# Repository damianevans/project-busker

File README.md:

# Project Busker

I promised I would build my daughter a busking amp for her Birthday. That was 18 months ago 😫
This project is based on the excellent hackaday article from David Silverman (details below).
The final plan is for a self-contained busking amp with the following features:
- 2 XLR microphone inputs, each with it's own pre-amp and reverb module.
- An electric guitar amp with effects, built using a raspberry pi 4 with an AudioInjector hat
- A hardware mixer
- a power amp

# David Silverman's guitarpedal links
Guitar Pedal for Raspberry pi using Python and PYO library 

Technical documentation being worked on here:

https://docs.google.com/presentation/d/1GgiD2UTEGcz-SC2rGDjdIljaK2Yn0Rs03TDFOu3duUw/edit?usp=sharing

Video demo here:

https://www.youtube.com/watch?v=wl24fLW1fQE

In depth code walkthrough here:

https://www.youtube.com/watch?v=LpFfZ5o4mEs

Looper video here:

https://youtu.be/jMI3nN0OYLE

Hackaday project here:

https://hackaday.io/project/186218-raspberry-pi-guitar-amplifier

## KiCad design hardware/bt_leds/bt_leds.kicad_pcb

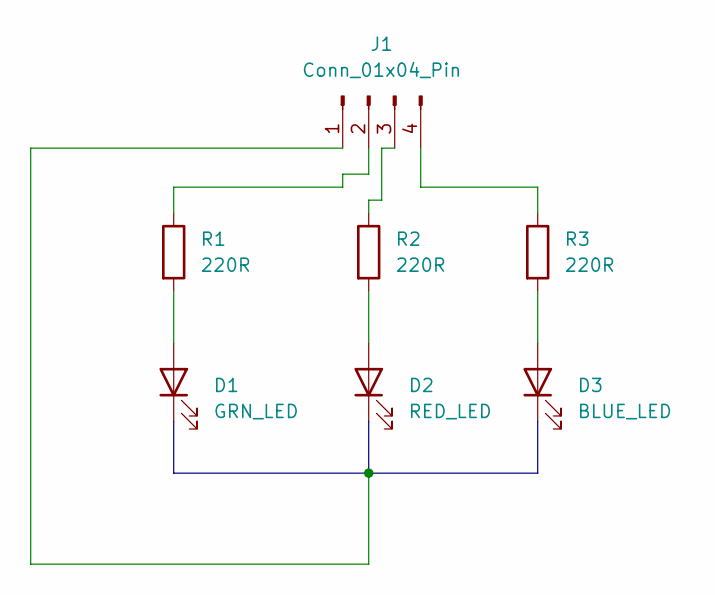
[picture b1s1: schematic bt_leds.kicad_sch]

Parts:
D1: GRN_LED; LED_Rectangular_W5.0mm_H2.0mm
D2: RED_LED; LED_Rectangular_W5.0mm_H2.0mm
D3: BLUE_LED; LED_Rectangular_W5.0mm_H2.0mm
J1: Conn_01x04_Pin; PinHeader_1x04_P2.54mm_Vertical
R1, R2, R3: 220R; R_Axial_DIN0207_L6.3mm_D2.5mm_P10.16mm_Horizontal

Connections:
unnamed: D1.2 (A), R1.2
unnamed: D1.1 (K), D2.1 (K), D3.1 (K), J1.1
unnamed: D2.2 (A), R2.2
unnamed: D3.2 (A), R3.2
unnamed: J1.2, R1.1
unnamed: J1.3, R2.1
unnamed: J1.4, R3.1

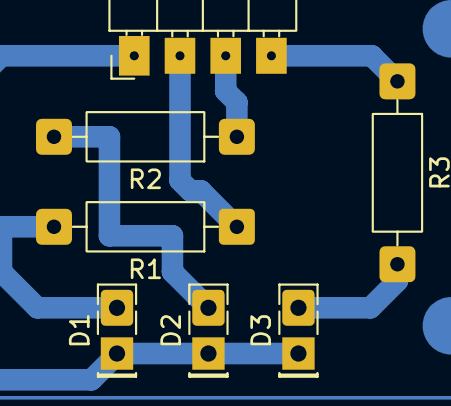
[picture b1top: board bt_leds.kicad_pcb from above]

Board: 2 copper layers, 7 parts (0 on the bottom side), 7 nets.

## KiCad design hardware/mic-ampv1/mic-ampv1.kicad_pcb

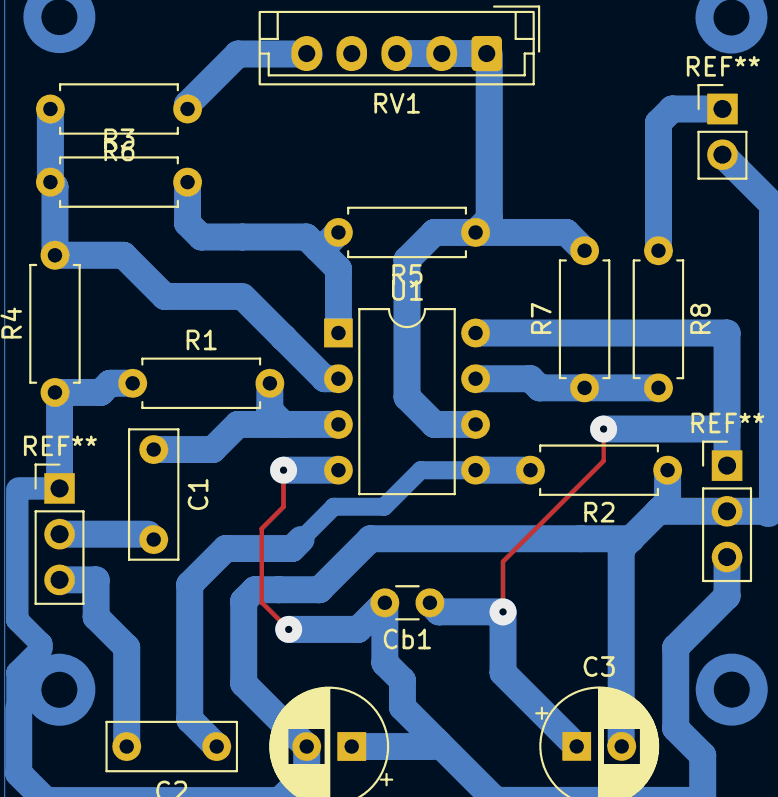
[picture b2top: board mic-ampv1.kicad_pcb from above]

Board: 2 copper layers, 15 parts (0 on the bottom side), 10 nets.

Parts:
C1, C2: 150nF; C_Rect_L7.0mm_W2.5mm_P5.00mm
C3, C4: 10uF; CP_Radial_D6.3mm_P2.50mm
Cb1: 100nF; C_Disc_D3.0mm_W1.6mm_P2.50mm
R1, R2, R3, R4, R5, R7: 10K; R_Axial_DIN0207_L6.3mm_D2.5mm_P7.62mm_Horizontal
R6: 47; R_Axial_DIN0207_L6.3mm_D2.5mm_P7.62mm_Horizontal
R8: 100; R_Axial_DIN0207_L6.3mm_D2.5mm_P7.62mm_Horizontal
RV1: 10K; JST_EH_B5B-EH-A_1x05_P2.50mm_Vertical
U1: NE5532; DIP-8_W7.62mm

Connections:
+12V: C3.1, Cb1.1, U1.8 (V+)
-12V: C4.1, Cb1.2, U1.4 (V-)
Gnd: C3.2, C4.2, R1.1, R2.1, R4.1
unnamed: R3.2, R5.2, U1.1
unnamed: R6.1, RV1.5
unnamed: R7.1, R8.2, U1.7
unnamed: C1.1, R1.2, U1.3 (+)
unnamed: R3.1, R4.2, R6.2, U1.2 (-)
unnamed: C2.1, R2.2, U1.5 (+)
unnamed: R5.1, R7.2, RV1.1, RV1.2, RV1.3, U1.6 (-)

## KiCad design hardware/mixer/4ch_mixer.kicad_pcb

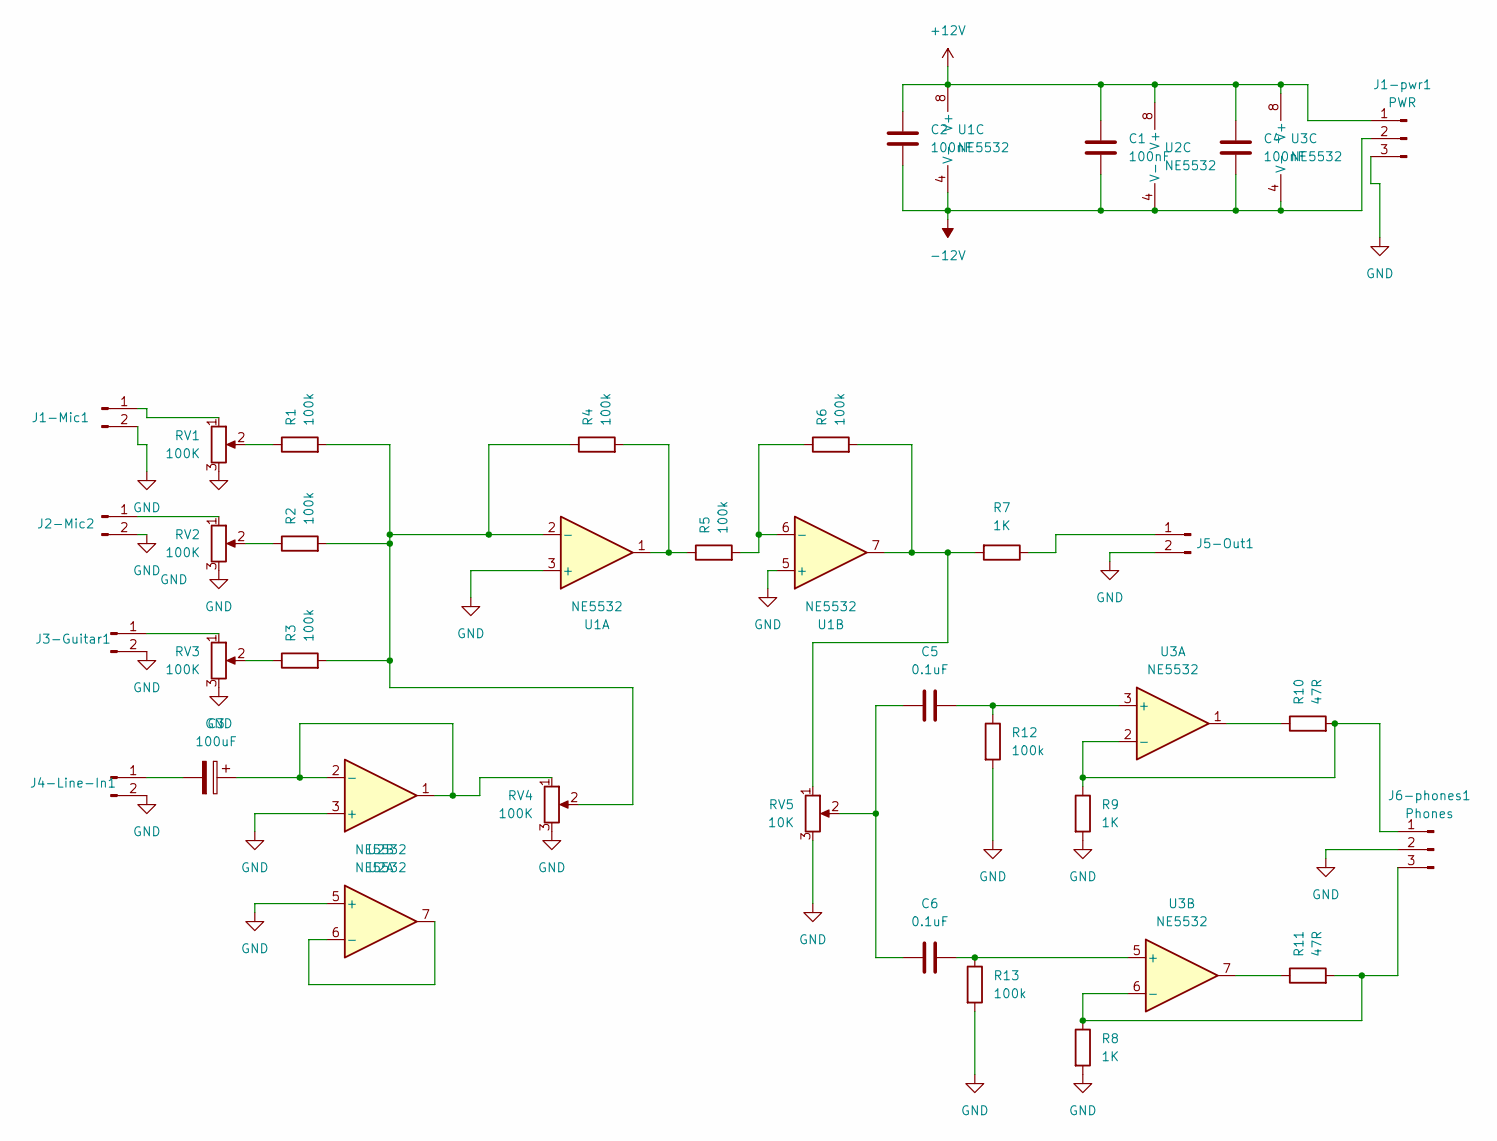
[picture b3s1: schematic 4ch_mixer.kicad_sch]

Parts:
C1, C2, C4: 100nF; C_Disc_D3.0mm_W1.6mm_P2.50mm
C3: 100uF; CP_Radial_D4.0mm_P1.50mm
C5, C6: 0.1uF; C_Rect_L11.0mm_W2.8mm_P10.00mm_MKT
J1-Mic1, J2-Mic2, J3-Guitar1, J4-Line-In1, J5-Out1: Conn_01x02_Pin; PinHeader_1x02_P2.54mm_Vertical
J1-pwr1: PWR; FanPinHeader_1x03_P2.54mm_Vertical
J6-phones1: Phones; FanPinHeader_1x03_P2.54mm_Vertical
R1, R2, R3, R4, R5, R6, R12, R13: 100k; R_Axial_DIN0204_L3.6mm_D1.6mm_P5.08mm_Horizontal
R7, R8, R9: 1K; R_Axial_DIN0204_L3.6mm_D1.6mm_P5.08mm_Horizontal
R10, R11: 47R; R_Axial_DIN0204_L3.6mm_D1.6mm_P5.08mm_Horizontal
RV1, RV2, RV3, RV4: 100K; PinHeader_1x03_P2.54mm_Vertical
RV5: 10K; PinHeader_1x03_P2.54mm_Vertical
U1, U2, U3: NE5532; CERDIP-8_W7.62mm_SideBrazed_LongPads

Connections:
+12V: C1.1, C2.1, C4.1, J1-pwr1.1, U1.8 (V+), U2.8 (V+), U3.8 (V+)
-12V: C1.2, C2.2, C4.2, J1-pwr1.2, U1.4 (V-), U2.4 (V-), U3.4 (V-)
GND: J1-Mic1.2, J1-pwr1.3, J2-Mic2.2, J3-Guitar1.2, J4-Line-In1.2, J5-Out1.2, J6-phones1.2, R8.2, R9.2, R12.2, R13.2, RV1.3, RV2.3, RV3.3, RV4.3, RV5.3, U1.3 (+), U1.5 (+), U2.3 (+), U2.5 (+)
unnamed: C5.1, C6.1, RV5.2
unnamed: J1-Mic1.1, RV1.1
unnamed: J2-Mic2.1, RV2.1
unnamed: J3-Guitar1.1, RV3.1
unnamed: C3.2, J4-Line-In1.1
unnamed: J5-Out1.1, R7.1
unnamed: J6-phones1.1, R9.1, R10.2, U3.2 (-)
unnamed: J6-phones1.3, R8.1, R11.2, U3.6 (-)
unnamed: R1.1, RV1.2
unnamed: R2.1, RV2.2
unnamed: R3.1, RV3.2
unnamed: R4.2, R5.1, U1.1
unnamed: R6.2, R7.2, RV5.1, U1.7
unnamed: R10.1, U3.1
unnamed: R11.1, U3.7
unnamed: R1.2, R2.2, R3.2, R4.1, RV4.2, U1.2 (-)
unnamed: R5.2, R6.1, U1.6 (-)
unnamed: C3.1, RV4.1, U2.1, U2.2 (-)
unnamed: U2.6 (-), U2.7
unnamed: C5.2, R12.1, U3.3 (+)
unnamed: C6.2, R13.1, U3.5 (+)

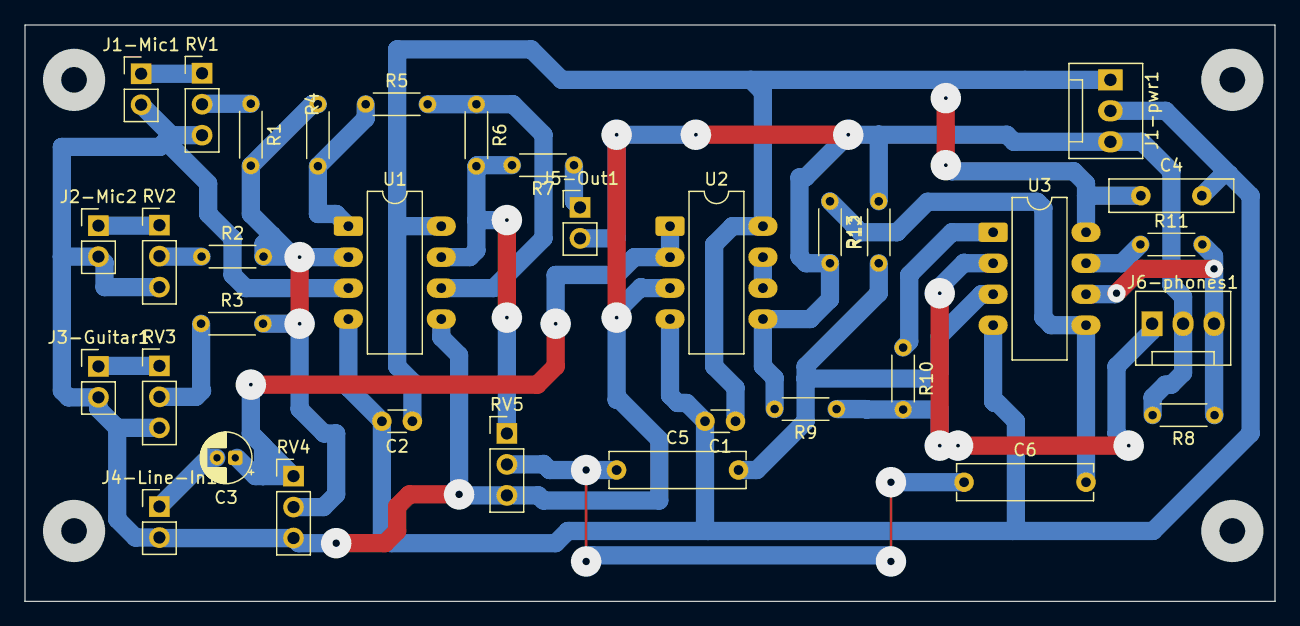
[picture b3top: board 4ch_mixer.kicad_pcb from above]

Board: 2 copper layers, 102.5 x 47.3 mm, 34 parts (0 on the bottom side), 24 nets.

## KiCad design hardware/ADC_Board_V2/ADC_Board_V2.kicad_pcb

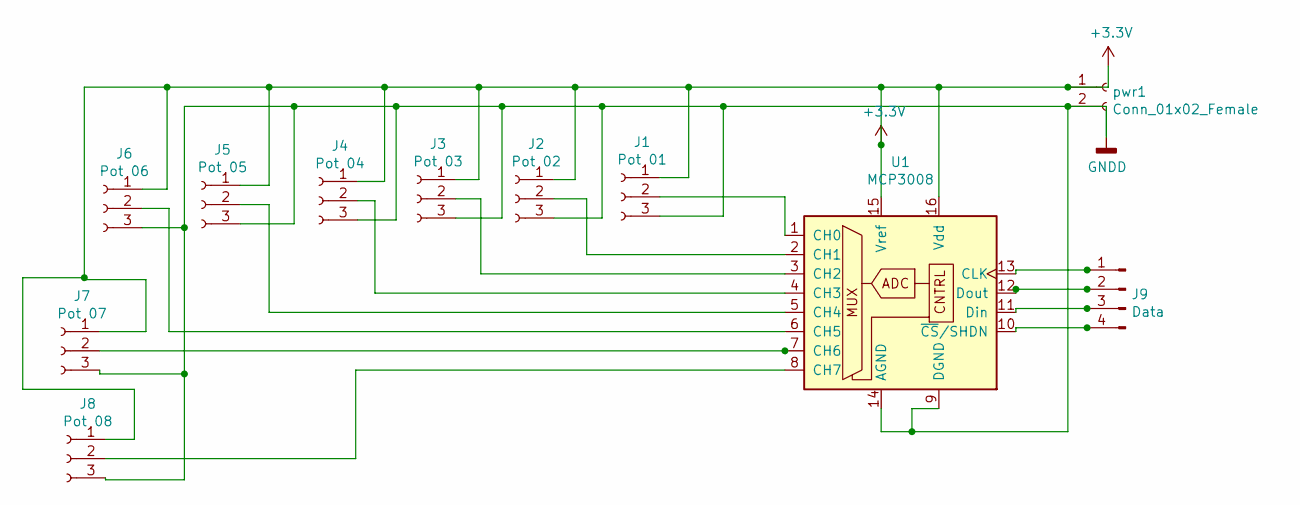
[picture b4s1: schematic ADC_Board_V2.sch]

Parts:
J1: Pot 01; JST_XH_B3B-XH-A_1x03_P2.50mm_Vertical
J2: Pot 02; JST_XH_B3B-XH-A_1x03_P2.50mm_Vertical
J3: Pot 03; JST_XH_B3B-XH-A_1x03_P2.50mm_Vertical
J4: Pot 04; JST_XH_B3B-XH-A_1x03_P2.50mm_Vertical
J5: Pot 05; JST_XH_B3B-XH-A_1x03_P2.50mm_Vertical
J6: Pot 06; JST_XH_B3B-XH-A_1x03_P2.50mm_Vertical
J7: Pot 07; JST_XH_B3B-XH-A_1x03_P2.50mm_Vertical
J8: Pot 08; JST_XH_B3B-XH-A_1x03_P2.50mm_Vertical
J9: Data; PinHeader_1x04_P2.54mm_Horizontal
U1: MCP3008; DIP-16_W7.62mm_Socket_LongPads
pwr1: Conn_01x02_Female; JST_XH_B2B-XH-AM_1x02_P2.50mm_Vertical

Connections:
+3V3: J1.1, J2.1, J3.1, J4.1, J5.1, J6.1, J7.1, J8.1, U1.15 (Vref), U1.16 (Vdd), pwr1.1
GNDD: J1.3, J2.3, J3.3, J4.3, J5.3, J6.3, J7.3, J8.3, U1.9 (DGND), U1.14 (AGND), pwr1.2
unnamed: J1.2, U1.1 (CH0)
unnamed: J2.2, U1.2 (CH1)
unnamed: J3.2, U1.3 (CH2)
unnamed: J4.2, U1.4 (CH3)
unnamed: J5.2, U1.5 (CH4)
unnamed: J6.2, U1.6 (CH5)
unnamed: J7.2, U1.7 (CH6)
unnamed: J8.2, U1.8 (CH7)
unnamed: J9.1, U1.13 (CLK)
unnamed: J9.2, U1.12 (Dout)
unnamed: J9.3, U1.11 (Din)
unnamed: J9.4, U1.10 (~CS~/SHDN)

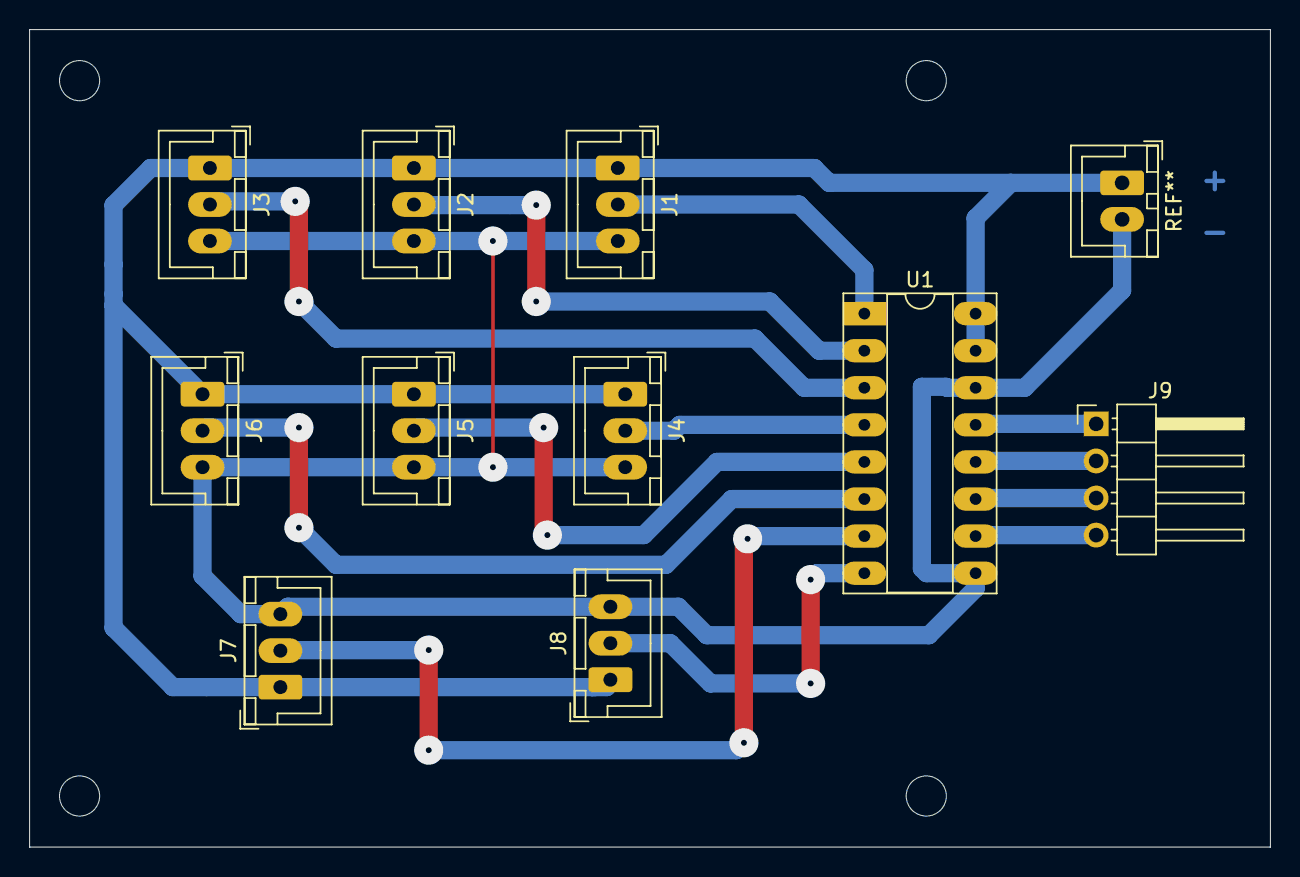
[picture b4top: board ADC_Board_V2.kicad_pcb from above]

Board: 2 copper layers, 85.0 x 56.0 mm, 10 parts (0 on the bottom side), 14 nets.

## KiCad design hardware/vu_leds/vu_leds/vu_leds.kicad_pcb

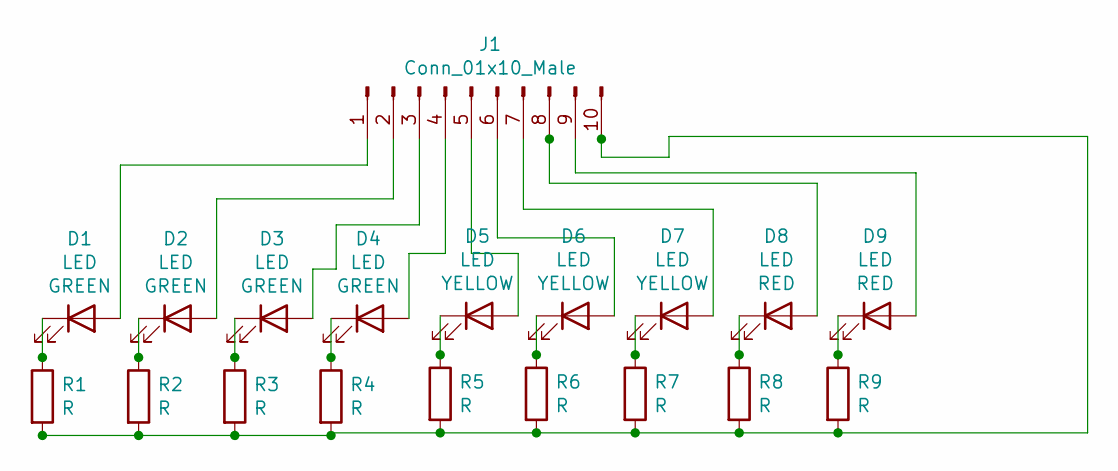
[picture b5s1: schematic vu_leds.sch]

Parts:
D1, D2, D3, D4, D5, D6, D7, D8, D9: LED; LED_Rectangular_W5.0mm_H2.0mm
J1: Conn_01x10_Male; PinHeader_1x10_P2.54mm_Horizontal
R1, R2, R3, R4, R5, R6, R7, R8, R9: R; R_Axial_DIN0207_L6.3mm_D2.5mm_P7.62mm_Horizontal

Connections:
unnamed: D1.1 (K), R1.1
unnamed: D1.2 (A), J1.1
unnamed: D2.1 (K), R2.1
unnamed: D2.2 (A), J1.2
unnamed: D3.1 (K), R3.1
unnamed: D3.2 (A), J1.3
unnamed: D4.1 (K), R4.1
unnamed: D4.2 (A), J1.4
unnamed: D5.1 (K), R5.1
unnamed: D5.2 (A), J1.5
unnamed: D6.1 (K), R6.1
unnamed: D6.2 (A), J1.6
unnamed: D7.1 (K), R7.1
unnamed: D7.2 (A), J1.7
unnamed: D8.1 (K), R8.1
unnamed: D8.2 (A), J1.8
unnamed: D9.1 (K), R9.1
unnamed: D9.2 (A), J1.9
unnamed: J1.10, R1.2, R2.2, R3.2, R4.2, R5.2, R6.2, R7.2, R8.2, R9.2

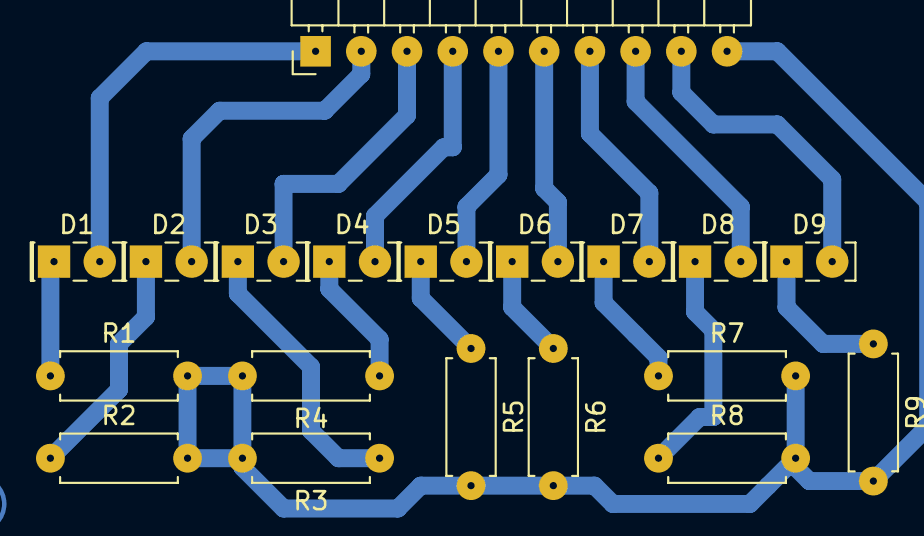
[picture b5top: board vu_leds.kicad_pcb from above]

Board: 2 copper layers, 19 parts (0 on the bottom side), 19 nets.

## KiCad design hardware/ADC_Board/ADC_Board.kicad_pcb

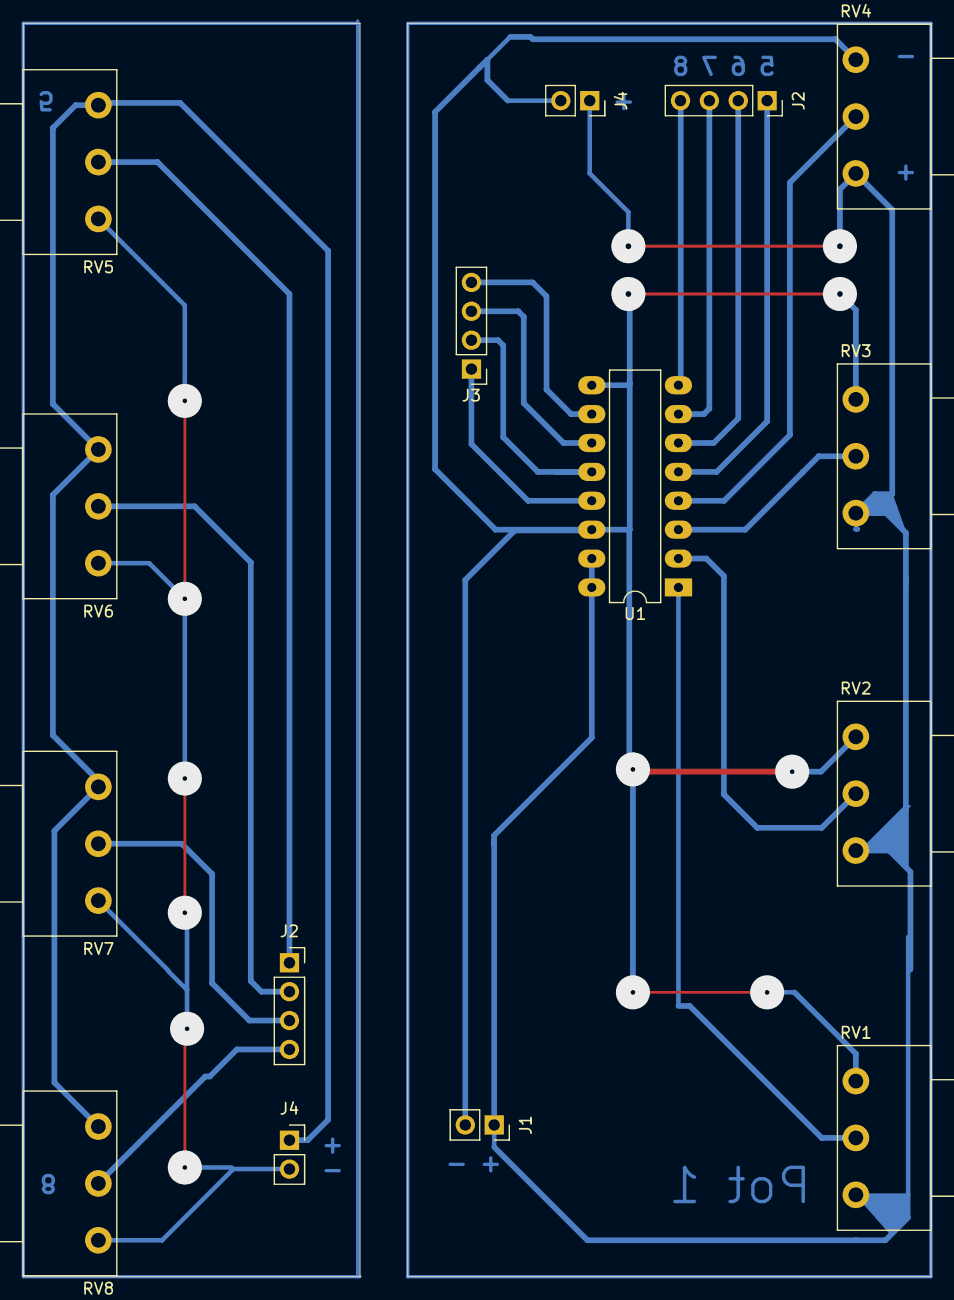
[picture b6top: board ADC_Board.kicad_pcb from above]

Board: 2 copper layers, 79.8 x 110.2 mm, 15 parts (0 on the bottom side), 12 nets.

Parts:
J1, J4, J4#2: Conn_01x02_Female; PinSocket_1x02_P2.54mm_Vertical
J2, J2#2: Conn_01x04_Female; PinSocket_1x04_P2.54mm_Vertical
J3: Conn_01x04_Female; PinHeader_1x04_P2.54mm_Vertical
RV1, RV2, RV3, RV4, RV5, RV6, RV7, RV8: R_POT; Potentiometer_Piher_PC-16_Single_Horizontal
U1: MCP3008; DIP-16_W7.62mm_LongPads

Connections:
unnamed: J2#2.1, U1.5
unnamed: J2#2.2, U1.6
unnamed: J2#2.3, U1.7
unnamed: J2#2.4, U1.8
unnamed: J3.1, U1.13
unnamed: J3.2, U1.12
unnamed: J3.3, U1.11
unnamed: J3.4, U1.10
unnamed: RV1.2, U1.1
unnamed: RV2.2, U1.2
unnamed: RV3.2, U1.3
unnamed: RV4.2, U1.4

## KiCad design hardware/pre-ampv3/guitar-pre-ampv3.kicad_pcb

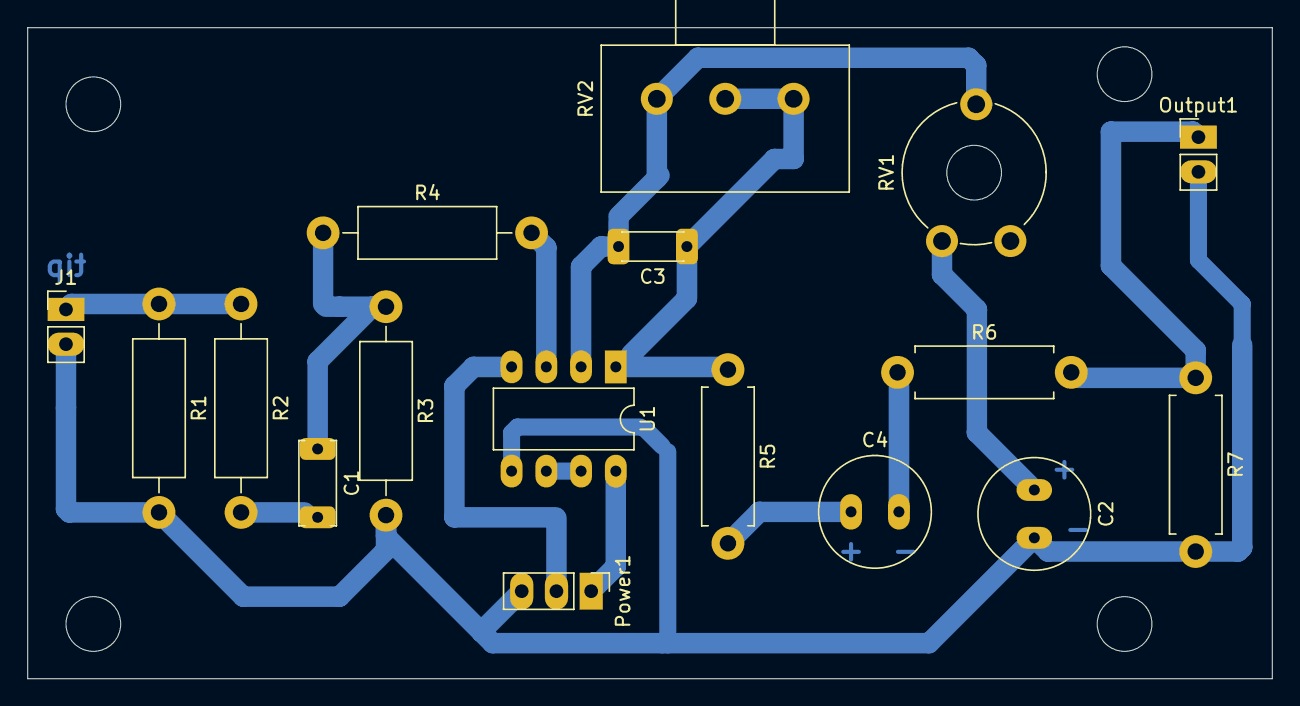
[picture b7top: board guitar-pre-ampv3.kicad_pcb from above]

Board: 2 copper layers, 91.0 x 47.6 mm, 17 parts (0 on the bottom side), 12 nets.

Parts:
C1: 100n; C_Disc_D6.0mm_W2.5mm_P5.00mm
C2, C4: 10uF; C_Radial_D8.0mm_H11.5mm_P3.50mm
C3: 100p; C_Disc_D4.3mm_W1.9mm_P5.00mm
J1: Input; PinHeader_1x02_P2.54mm_Vertical
Output1: Conn_01x02_Male; PinHeader_1x02_P2.54mm_Vertical
Power1: pwr; PinHeader_1x03_P2.54mm_Vertical
R1: 470k; R_Axial_DIN0411_L9.9mm_D3.6mm_P15.24mm_Horizontal
R2, R4: 1k; R_Axial_DIN0411_L9.9mm_D3.6mm_P15.24mm_Horizontal
R3: 470K; R_Axial_DIN0411_L9.9mm_D3.6mm_P15.24mm_Horizontal
R5, R6: 1k; R_Axial_DIN0411_L9.9mm_D3.6mm_P12.70mm_Horizontal
R7: 100k; R_Axial_DIN0411_L9.9mm_D3.6mm_P12.70mm_Horizontal
RV1: 10K; Potentiometer_Piher_PT-10-V10_Vertical_Hole
RV2: 50k; Potentiometer_Alps_RK163_Single_Horizontal
U1: NE5532; DIP-8_W7.62mm_LongPads

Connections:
GND: C2.2, J1.2, Output1.2, Power1.3, R1.2, R3.2, R7.2, U1.5
unnamed: C1.1, R3.1, R4.1
unnamed: C1.2, R2.2
unnamed: C2.1, RV1.3
unnamed: C3.1, RV2.1, RV2.2
unnamed: C3.2, RV1.1, RV1.2, RV2.3, U1.2
unnamed: C4.1, R5.2
unnamed: C4.2, R6.1
unnamed: J1.1, R1.1, R2.1
unnamed: Output1.1, R6.2, R7.1
unnamed: R4.2, U1.3
unnamed: R5.1, U1.1

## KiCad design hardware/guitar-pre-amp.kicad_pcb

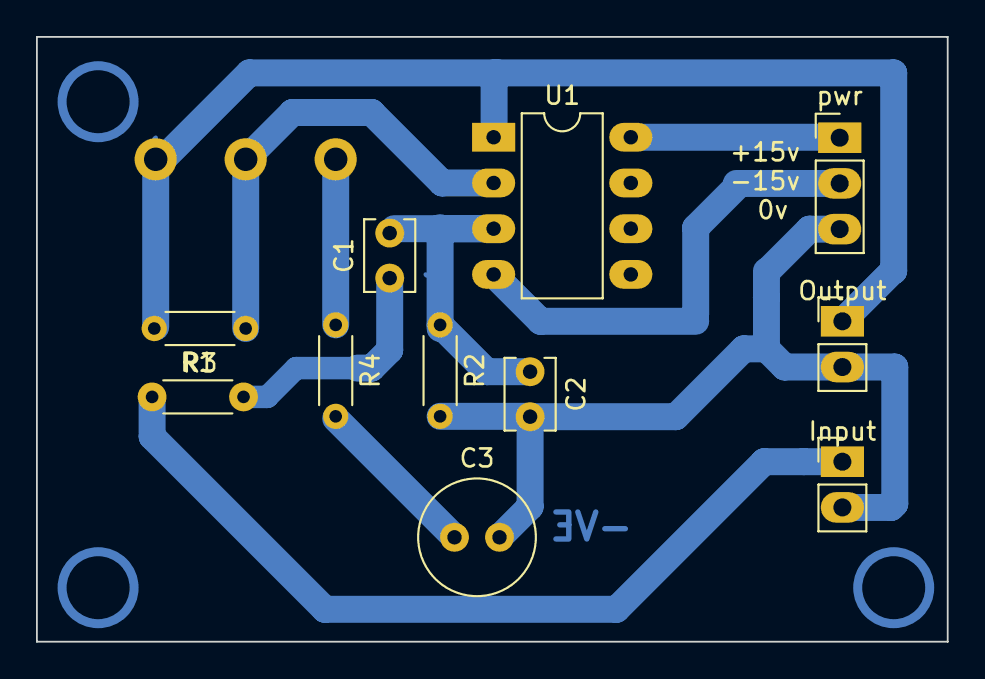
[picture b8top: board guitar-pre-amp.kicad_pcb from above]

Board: 2 copper layers, 50.6 x 33.6 mm, 12 parts (1 on the bottom side), 8 nets.

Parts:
C1: 100nF; C_Disc_D3.8mm_W2.6mm_P2.50mm
C2: 100pF; C_Disc_D3.8mm_W2.6mm_P2.50mm
C3: 100uF; C_Radial_D6.3mm_H5.0mm_P2.50mm
Input: PinHeader_1x02_P2.54mm_Vertical
Output: .; PinHeader_1x02_P2.54mm_Vertical
R1: 100; R_Axial_DIN0204_L3.6mm_D1.6mm_P5.08mm_Horizontal
R2: 1M; R_Axial_DIN0204_L3.6mm_D1.6mm_P5.08mm_Horizontal
R3: 100K; R_Axial_DIN0204_L3.6mm_D1.6mm_P5.08mm_Horizontal
R4: 330; R_Axial_DIN0204_L3.6mm_D1.6mm_P5.08mm_Horizontal
RV1: 100K; Potentiometer_Alps_RK163_Single_Horizontal
U1: NE5532; DIP-8_W7.62mm_LongPads
pwr: .; PinHeader_1x03_P2.54mm_Vertical

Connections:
GND: C2.2, C3.2, Input.2, Output.2, R2.2, pwr.3
unnamed: C1.1, R1.2
unnamed: C1.2, C2.1, R2.1, U1.3
unnamed: C3.1, R4.2
unnamed: Input.1, R1.1
unnamed: Output.1, R3.2, RV1.1, U1.1
unnamed: R3.1, RV1.2, U1.2
unnamed: R4.1, RV1.3

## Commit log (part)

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2024-09-02 added guitarpedal files
2024-09-07 changed sliders to regular wx sliders
2024-09-22 commented out effects
2024-09-22 set in / out devices
2025-04-27 started prod version
2025-04-27 effects not working yet
2025-04-27 added Circuit schematics and PCB layouts
2025-04-27 fix data url for OSC
2025-05-04 getting knobs working
2025-05-04 fx working. Wah is crap though
2025-05-22 Create looper-footpedal
2025-05-22 Updated sequence
2025-05-24 merging buttons & bluetooth code
2025-05-28 complete buttons and BLE bluetooth send
2025-05-28 added working bt receiver
2025-05-30 adding bt client into busker loop
2025-05-30 missing asyncio
2025-05-30 fix string() -> str()
2025-05-30 tidy up logging messages
2025-05-30 fix async send call
2025-05-30 fix oldlooperState
2025-05-30 update connection error message
2025-05-30 force wait for confirmation of erase
2025-05-30 moved files for Arduino ide compatibility
2025-05-30 fix Erase event
2025-05-31 add bt status light to pi
2025-05-31 fix led pin conflict
2025-05-31 use external led on ESP32
2025-05-31 added looper code ensure loop state is uppercase
2025-05-31 blue led status
2025-05-31 looper state init
2025-05-31 loop_rec global
2025-05-31 led flash
2025-05-31 esp32 tweak startup sequence
2025-05-31 lights sequence
2025-06-04 change threading. fix record & play options
2025-06-04 looper don't work
2025-06-04 remove all async thread and record
2025-06-04 not honoring fx values
2025-06-04 remove loops state
2025-06-04 fix sleep
2025-06-04 re-apply bt loop
2025-06-04 add chorus
2025-06-08 added console output
2025-06-08 fix console bug
2025-06-08 console issues
2025-06-08 copilot is donkeyballs sometimes
2025-06-08 claude ai console display
2025-06-08 moved display to a new library
2025-06-08 change delay for chorus
2025-06-08 delay -> chorus
2025-06-08 chorus tweaks
2025-06-08 more chorus tweaks
2025-06-08 added looper code back in
2025-06-08 add OSC status to debug looper
2025-06-08 won't start up anymore :-(
2025-06-08 fix rms meter callback
2025-06-08 tweak display. tweak record
2025-06-08 revert back to orig looper
2025-06-08 fixing looper
2025-06-08 added separate mixers
2025-06-11 messing with mixer to get looper working
2025-06-11 removed mix for loop
2025-06-11 debug message for recording
2025-06-11 debug messages
2025-06-11 loop state was lowercase
2025-06-11 python intellisense is shit
2025-06-11 global variables, eh?
2025-06-11 recoring works, trying to fix play
2025-06-11 adding loop_play to mixer
2025-06-11 try adding loop_play back into mixer
2025-06-11 loop_file & silence now global
2025-06-11 hard-coded loop file
2025-06-11 PLAYBACK, NOT PLAYING you twat!!!
2025-06-11 remove mix add debug message
2025-06-11 it bloody works!!! Increased loop volume
2025-06-11 tidy up commented out code
2025-06-15 VU Leds PCB Layout added
2025-06-17 pdf of pcb layout
2025-06-17 made pcb smaller
2025-07-12 updated pins diagram AI generated mixer sch (not very good)
2025-07-12 changed vu leds
2025-07-12 changed VU Graph status. Fix NumLeds
2025-08-31 complete pcb for mic
2025-09-09 new board layout
2025-11-28 updated ADC board design
2025-11-28 new mixer design & headphones
2025-11-30 nearly finished mixer & phones
2025-12-07 Completed PCB layout
2026-02-14 Added GPIO pin numbers to led designations. Assigned pins for looper leds
2026-02-14 pending updates 14/02/26
2026-02-14 pulled leds png file into main
2026-02-14 reset looper leds state
2026-02-14 Added looper led states
2026-03-06 Update VU meter for right channel and clean up code
    Refactor VU meter handling for right channel and remove unused looper state code.
2026-03-06 Add looper state handling and playback controls
2026-03-06 Optimize audio processing and improve error handling
    Optimized audio processing with improved performance and error handling. Enhanced logging and simplified effect chain.
2026-03-21 Updated mic pre-amp. Longer board to help with layout. increase gain by changing R6 ->47 Ohm
2026-03-21 Updated mic preamp. Increased gain. larger PCB
